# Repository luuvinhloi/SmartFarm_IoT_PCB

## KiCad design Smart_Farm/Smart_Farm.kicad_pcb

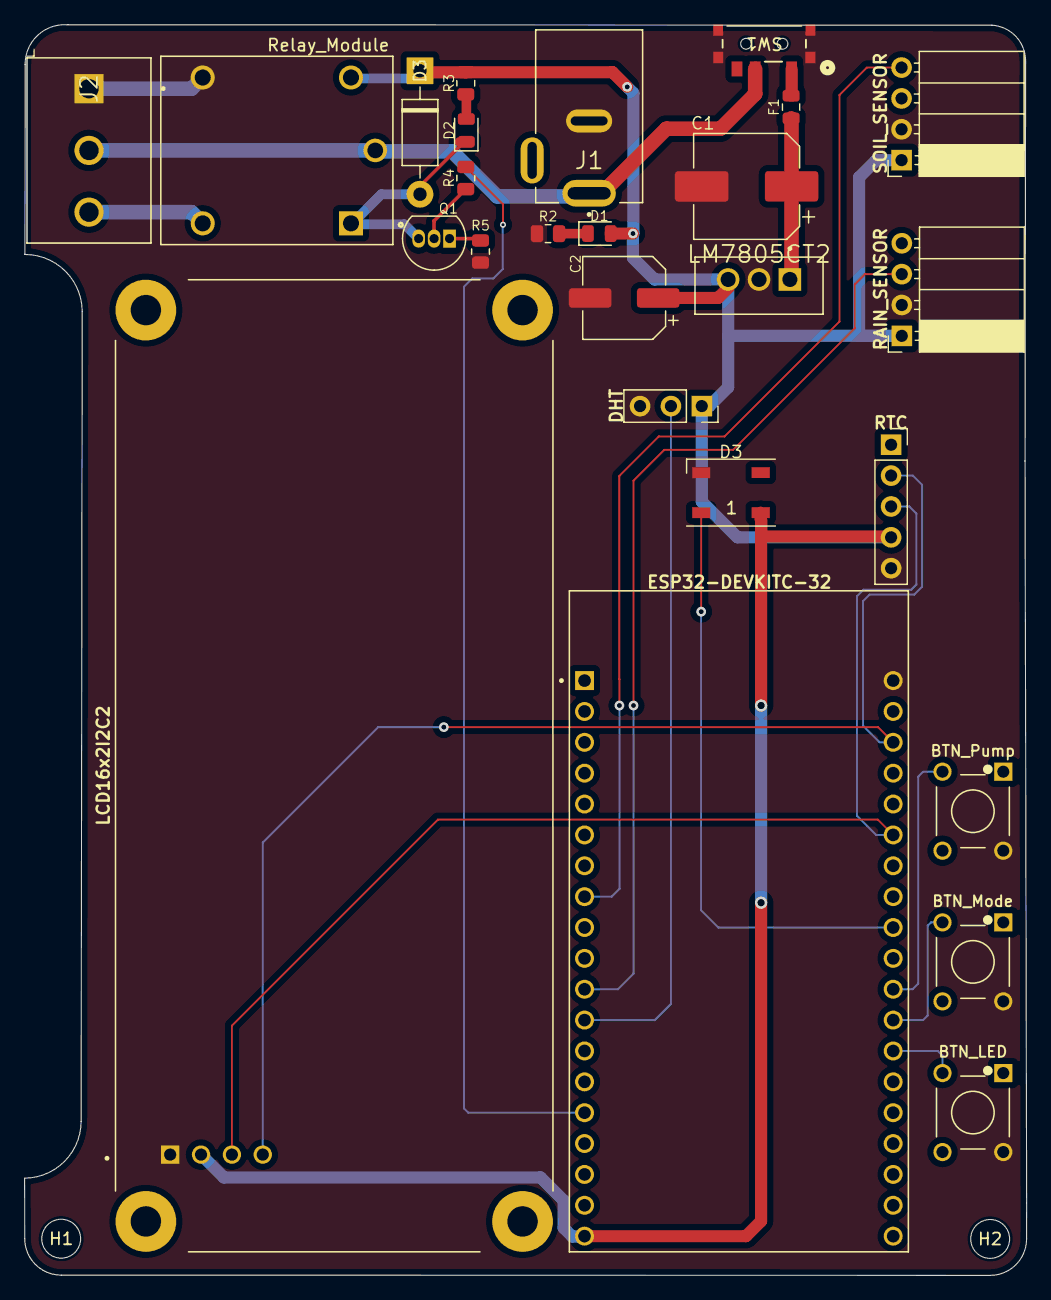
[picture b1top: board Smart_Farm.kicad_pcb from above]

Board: 2 copper layers, 82.5 x 102.9 mm, 28 parts (0 on the bottom side), 21 nets.

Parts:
BTN_LED: FSM8JH; Button
BTN_Mode: FSM8JH; Button
BTN_Pump: FSM8JH; Button
C1: 470uF; CP_Elec_8x10.5
C2: 100uF; CP_Elec_6.3x5.4
D1, D2: LED; LED_0805_2012Metric
D3: 1N4007; D_DO-41_SOD81_P10.16mm_Horizontal
D3#2: WS2812B; LED_WS2812B_PLCC4_5.0x5.0mm_P3.2mm
DHT: DHT11; PinSocket_1x03_P2.54mm_Vertical
ESP32-DEVKITC-32: ESP32-DEVKITC-32D; MODULE_ESP32-DEVKITC-32D
F1: Fuse; Fuse_0805_2012Metric
H1, H2: MountingHole; MountingHole_3.2mm_M3_ISO14580
J1: EJ508A; MPD_EJ508A
J2: Screw_Terminal_01x03; CUI_TB004-508-03BE
LCD16x2I2C2: LCD 16x2 I2C; LCD_LCD2X16
LM7805CT2: LM7805CT
Q1: 2N3904; TO-92_Inline
R2, R3, R4: 1k; R_0805_2012Metric
R5: 10k; R_0805_2012Metric
RAIN_SENSOR: RAIN SENSOR; PinSocket_1x04_P2.54mm_Horizontal
RTC: RTC; PinSocket_1x05_P2.54mm_Vertical
Relay_Module: Relay Module; RELAY_SRD-05VDC-SL-C
SOIL_SENSOR: SOIL SENSOR; PinSocket_1x04_P2.54mm_Horizontal
SW1: MK-12C02-G020; MK-12C02-G020_GSW

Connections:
+5V: C2.1, D1.2 (A), D3.1 (K), D3#2.1 (VDD), DHT.1 (VCC), ESP32-DEVKITC-32.J2-19 (EXT_5V), LCD16x2I2C2.2 (VCC), LM7805CT2.3 (OUT), R3.2, RAIN_SENSOR.1 (VCC), RTC.4 (VCC), Relay_Module.A2, SOIL_SENSOR.1 (VCC)
+12V: C1.1, F1.1, LM7805CT2.1 (IN)
/+12V Power: J1.1, J2.2, Relay_Module.COM, SW1.2
/IO_04: BTN_LED.2, ESP32-DEVKITC-32.J3-13 (IO4)
/IO_13: ESP32-DEVKITC-32.J2-15 (IO13), R4.1
/IO_14: DHT.2 (DAT), ESP32-DEVKITC-32.J2-12 (IO14)
/IO_16: BTN_Mode.2, ESP32-DEVKITC-32.J3-12 (IO16)
/IO_17: BTN_Pump.2, ESP32-DEVKITC-32.J3-11 (IO17)
/IO_18: D3#2.4 (DIN), ESP32-DEVKITC-32.J3-9 (IO18)
/IO_21: ESP32-DEVKITC-32.J3-6 (IO21), LCD16x2I2C2.3 (SDA), RTC.3 (SDA)
/IO_22: ESP32-DEVKITC-32.J3-3 (IO22), LCD16x2I2C2.4 (SCL), RTC.2 (SCL)
/IO_27: ESP32-DEVKITC-32.J2-11 (IO27), RAIN_SENSOR.3 (DO)
/IO_33: ESP32-DEVKITC-32.J2-8 (IO33), SOIL_SENSOR.4 (AO)
GND: BTN_LED.3, BTN_Mode.3, BTN_Pump.3, C1.2, C2.2, D3#2.3 (VSS), DHT.3 (GND), ESP32-DEVKITC-32.J3-1 (GND3), J1.2, J2.1, LCD16x2I2C2.1 (GND), LM7805CT2.2 (GND), R2.1, R5.1, RAIN_SENSOR.2 (GND), RTC.5 (GND), Relay_Module.NO, SOIL_SENSOR.2 (GND), SW1.4, SW1.5, SW1.6, SW1.7
unnamed: D1.1 (K), R2.2
unnamed: D2.1 (K), D3.2 (A), Q1.3 (C), Relay_Module.A1
unnamed: D2.2 (A), R3.1
unnamed: F1.2, SW1.1
unnamed: J2.3, Relay_Module.NC
unnamed: Q1.2 (B), R4.2
unnamed: Q1.1 (E), R5.2

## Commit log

2025-03-04 Initial commit with PCB project files
2025-03-16 Update Schematic and PCB
2025-03-22 Update files
2025-03-22 Update images
